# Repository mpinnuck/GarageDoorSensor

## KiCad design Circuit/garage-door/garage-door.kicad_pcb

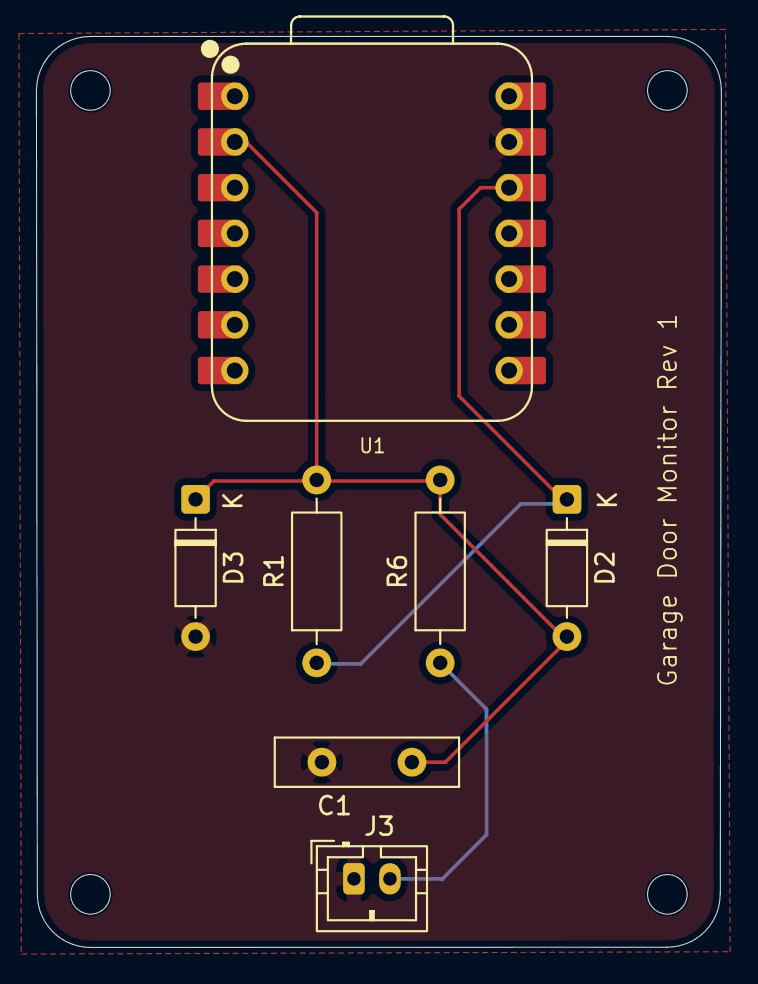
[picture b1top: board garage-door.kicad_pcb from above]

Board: 2 copper layers, 38.0 x 50.6 mm, 7 parts (0 on the bottom side), 4 nets.

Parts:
C1: 100nF; C_Disc_D10.0mm_W2.5mm_P5.00mm
D2, D3: 1N4148; D_DO-35_SOD27_P7.62mm_Horizontal
J3: JST PH 2-pin; JST_PH_B2B-PH-K_1x02_P2.00mm_Vertical
R1: 10k; R_Axial_DIN0207_L6.3mm_D2.5mm_P10.16mm_Horizontal
R6: 1k; R_Axial_DIN0207_L6.3mm_D2.5mm_P10.16mm_Horizontal
U1: XIAO-ESP32-C3-DIP; XIAO-ESP32C3-DIP

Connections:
+3V3: D2.1 (K), R1.1, U1.12 (VCC_3V3)
GND: C1.2, D3.2 (A), J3.1, U1.13 (GND)
unnamed: C1.1, D2.2 (A), D3.1 (K), R1.2, R6.2, U1.2 (GPIO3/A1/D1)
unnamed: J3.2, R6.1
